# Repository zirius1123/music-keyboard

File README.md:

# My Personal Midi Keyboard

## Components
I made a basic MIDI keyboard. This MIDI keyboard consists of the following:
-  3 LEDs
- 2 Slider Potentiometors
- 1 Rotary Potentiometor
- 6 Switches
- 1 Microcontroller
- 5 Touch Pads
- Some illustrations of halflife, hack club, and gato

## Explaining my PCB
The keyboard is centered around the Waveshare ESP32-S3-Zero. I used JLCPCB for the PCB production. I am using Aliexpress for the components needed.

The image above is of my PCB in the 3d viewer. I layed out the key switches by useing a 3x2 keyboard matrix to save 1 port. I also put the 3 LEDs in a row underneath the switches
Next to the switches is the two sliders and next to that is the Waveshare and the rotary potentiometer. 

## PCB Editor layout

This is the image of the PCB editor in which I made this.

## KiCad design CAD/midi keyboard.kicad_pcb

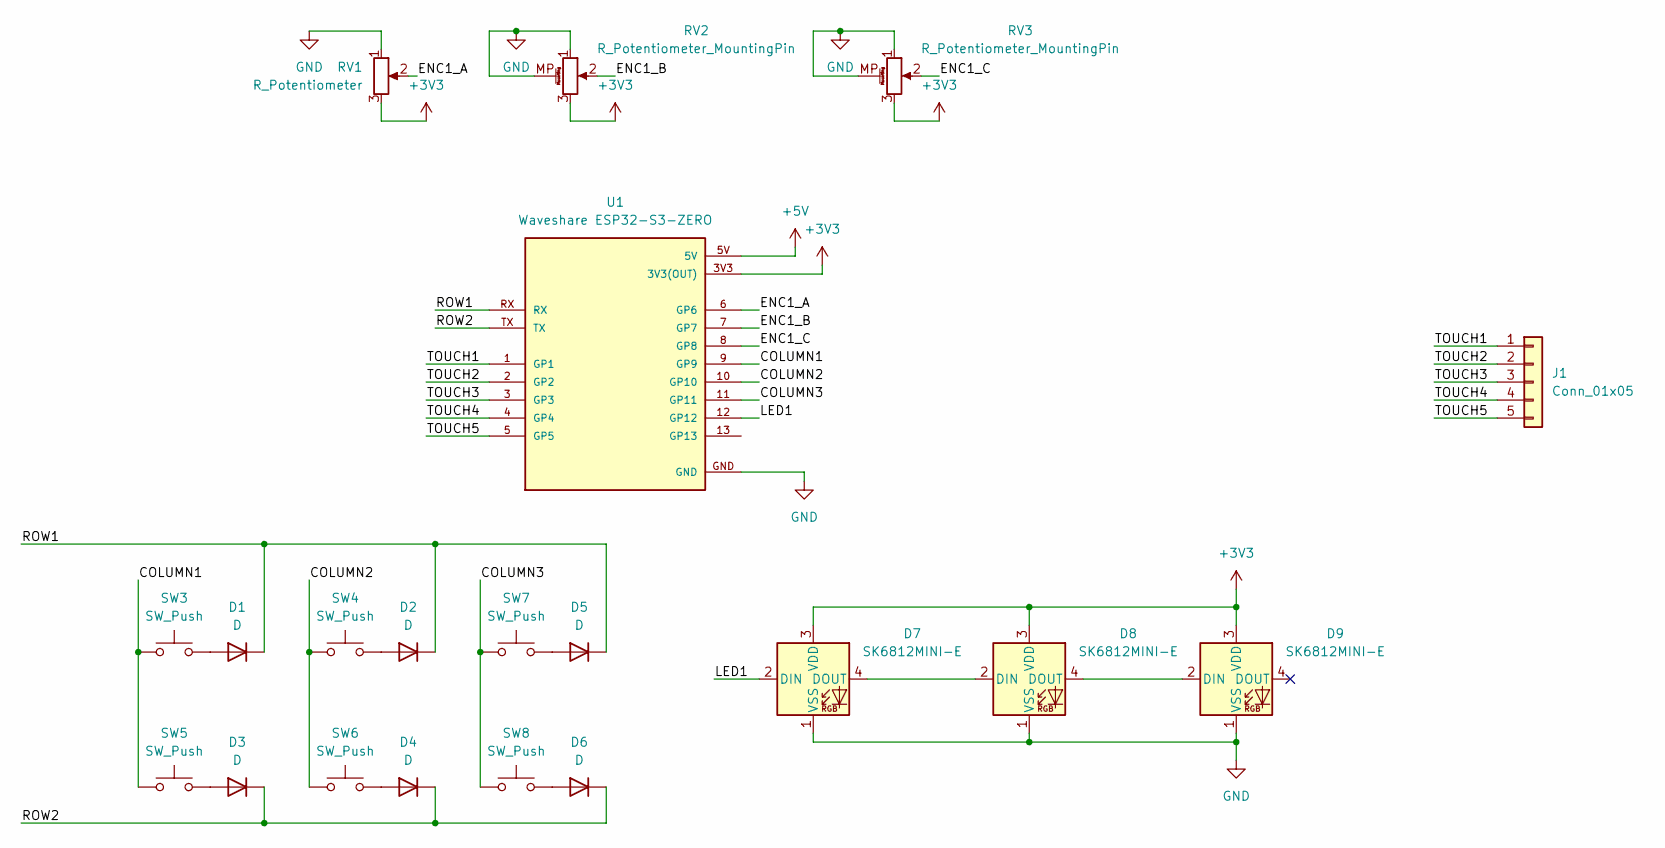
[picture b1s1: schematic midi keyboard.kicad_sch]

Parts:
D1, D2, D3, D4, D5, D6: D; D_SOD-123
D7, D8, D9: SK6812MINI-E; LED_SK6812MINI-E_3.2x2.8mm_P1.5mm_ReverseMount
J1: Conn_01x05; Capacitive_Keys_5_Armor (1)
RV1: R_Potentiometer; Potentiometer_Alps_RK09K_Single_Vertical
RV2, RV3: R_Potentiometer_MountingPin; Potentiometer_Bourns_PTA3043_Single_Slide
SW3, SW4, SW5, SW6, SW7, SW8: SW_Push; Kailh Choc Low-Profile Switches
U1: Waveshare ESP32-S3-ZERO; Waveshare ESP32-S3-Zero; PARTREV NA

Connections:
+3V3: D7.3 (VDD), D8.3 (VDD), D9.3 (VDD), RV1.3, RV2.3, RV3.3, U1.3V3 (3V3(OUT))
+5V: U1.5V
/COLUMN1: SW3.1, SW5.1, U1.9 (GP9)
/COLUMN2: SW4.1, SW6.1, U1.10 (GP10)
/COLUMN3: SW7.1, SW8.1, U1.11 (GP11)
/ENC1_A: RV1.2, U1.6 (GP6)
/ENC1_B: RV2.2, U1.7 (GP7)
/ENC1_C: RV3.2, U1.8 (GP8)
/LED1: D7.2 (DIN), U1.12 (GP12)
/ROW1: D1.1 (K), D2.1 (K), D5.1 (K), U1.RX
/ROW2: D3.1 (K), D4.1 (K), D6.1 (K), U1.TX
/TOUCH1: J1.1, U1.1 (GP1)
/TOUCH2: J1.2, U1.2 (GP2)
/TOUCH3: J1.3, U1.3 (GP3)
/TOUCH4: J1.4, U1.4 (GP4)
/TOUCH5: J1.5, U1.5 (GP5)
GND: D7.1 (VSS), D8.1 (VSS), D9.1 (VSS), RV1.1, RV2.1, RV2.MP (MountPin), RV3.1, RV3.MP (MountPin), U1.GND
unnamed: D1.2 (A), SW3.2
unnamed: D2.2 (A), SW4.2
unnamed: D3.2 (A), SW5.2
unnamed: D4.2 (A), SW6.2
unnamed: D5.2 (A), SW7.2
unnamed: D6.2 (A), SW8.2
unnamed: D7.4 (DOUT), D8.2 (DIN)
unnamed: D8.4 (DOUT), D9.2 (DIN)

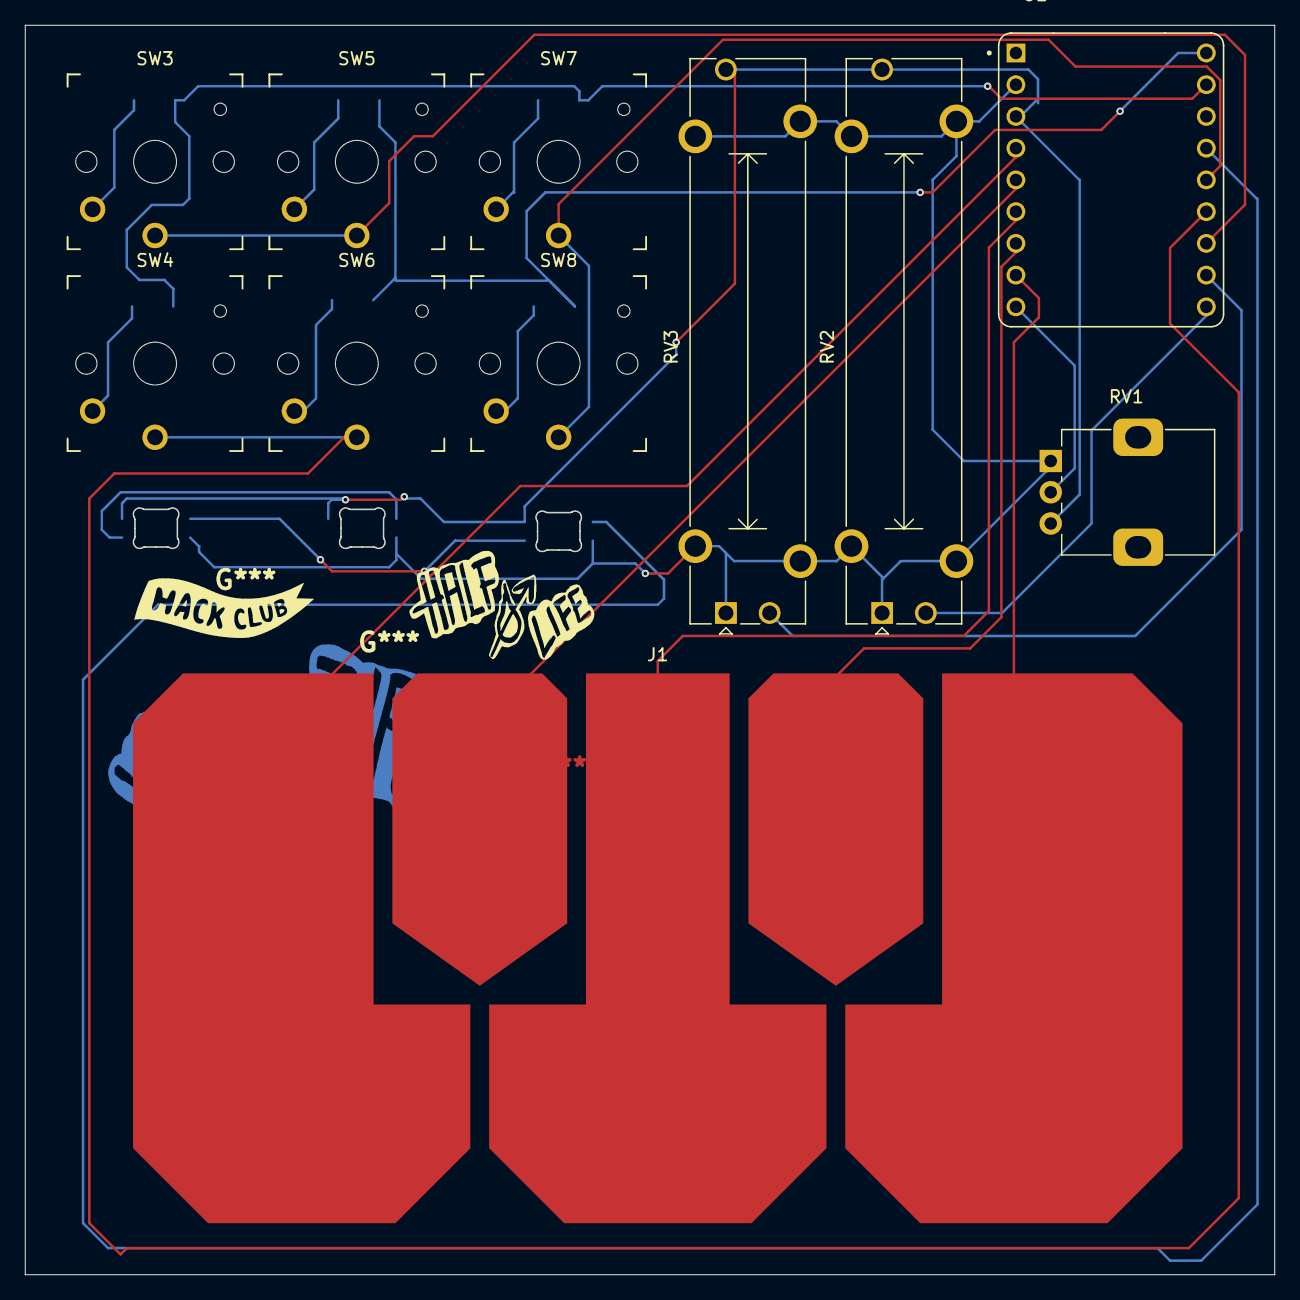
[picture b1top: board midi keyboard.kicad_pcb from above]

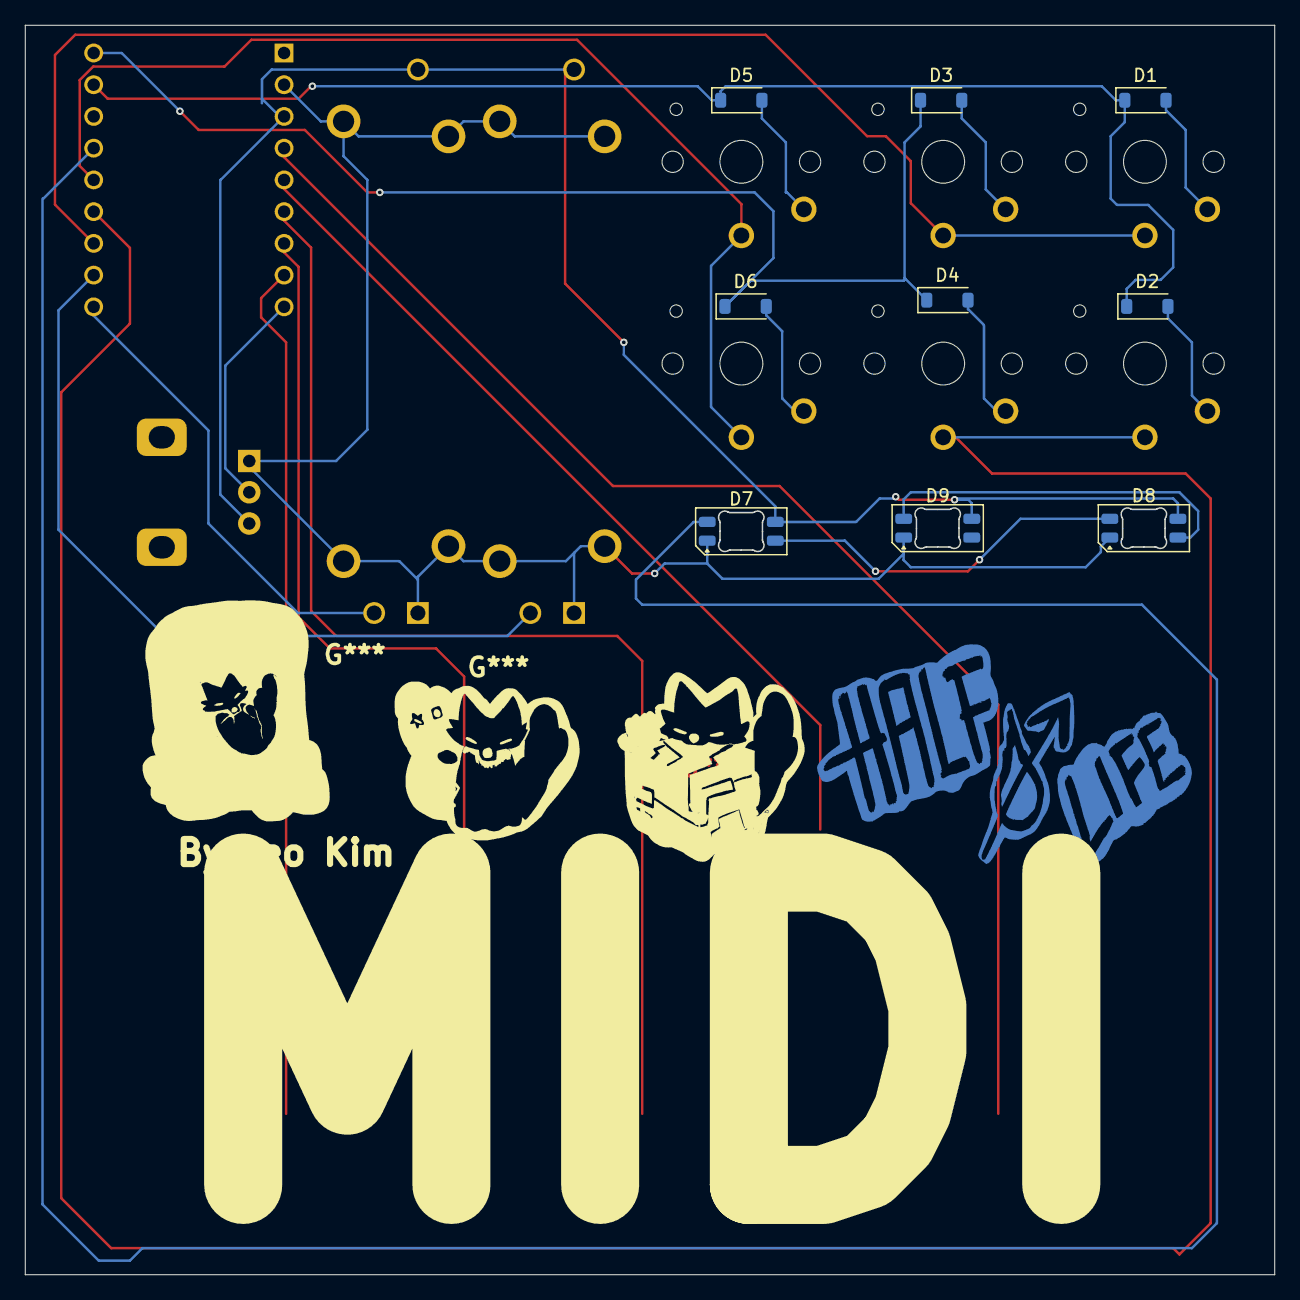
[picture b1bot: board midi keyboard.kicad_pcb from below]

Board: 2 copper layers, 100.0 x 100.0 mm, 20 parts (9 on the bottom side), 24 nets.
